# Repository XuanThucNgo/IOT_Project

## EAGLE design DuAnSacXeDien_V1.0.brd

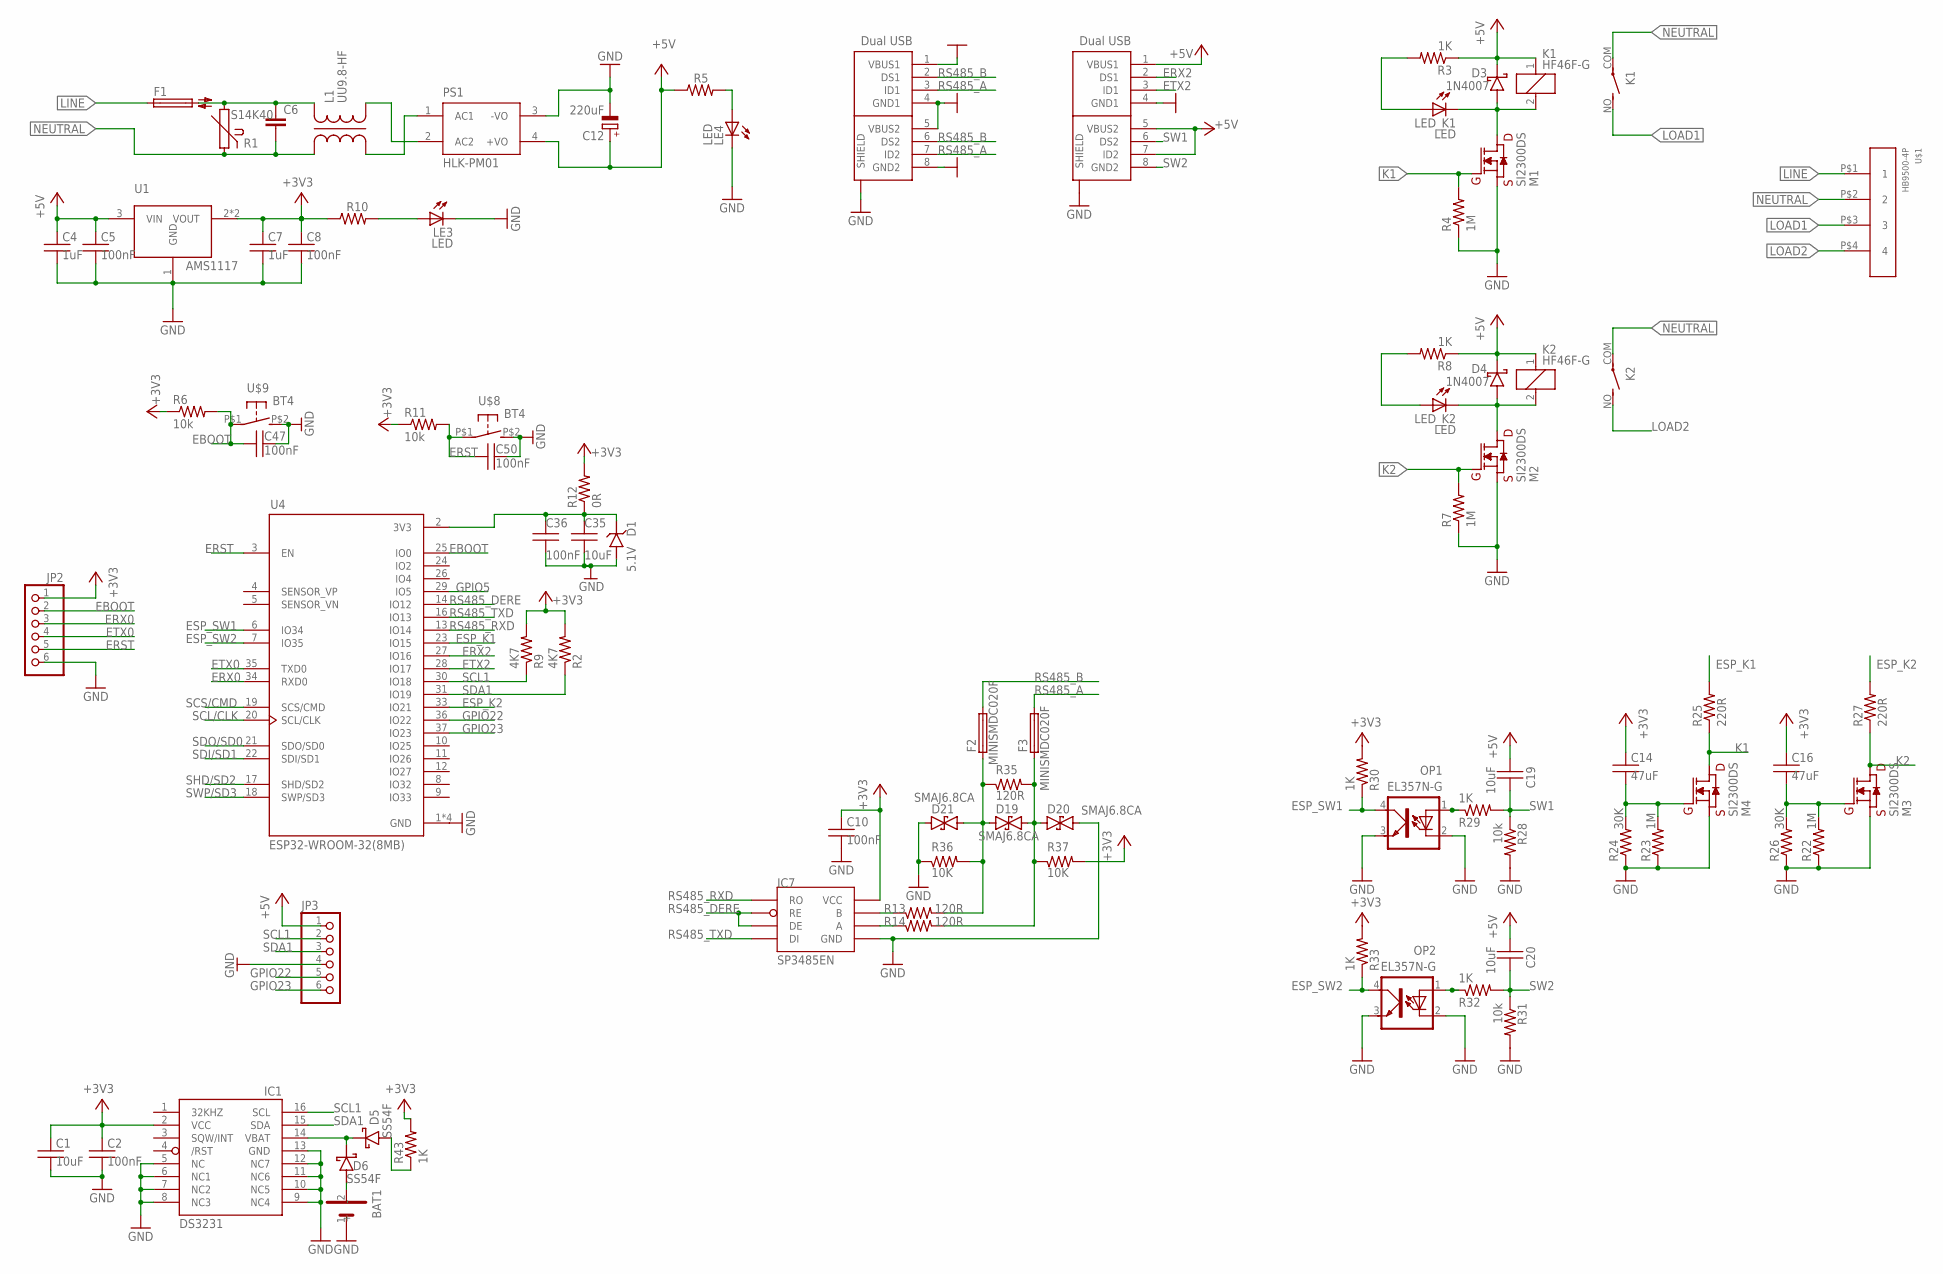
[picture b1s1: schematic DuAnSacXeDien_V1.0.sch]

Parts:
BAT1: CR1220
C1, C19, C20, C35: 10uF; 0603
C2, C5, C8, C10, C36, C47, C50: 100nF; 0603
C4, C7: 1uF; 0603
C6: C-EU150-064X183; C150-064X183
C12: 220uF; 153CLV-0605
C14, C16: 47uF; 0805
D1: 5.1V; SOD123
D3, D4: 1N4007; SMAF
D5, D6: SS54F; SMAF
D19, D20, D21: SMAJ6.8CA; DO-214AC-BI
F1: TE5
F2, F3: MINISMDC020F; C1812
IC1: DS3231/SO; SO16W
IC7: SP3485EN; SOIC-8
JP2: PINHD-1X6; 1X06
JP3: PINHD-1X6/LONG; 1X06
K1, K2: HF46F-G; LD
L1: UU9.8-HF
LE3, LE4: LED; LED3MM
LED_K1, LED_K2: LED; LED3MM
M1, M2, M3, M4: SI2300DS; SOT23(1)
OP1, OP2: EL357N-G; SOP4
PS1: HLK-PM01; HLK-PMXX
R1: S14K40
R2, R9: 4K7; 0603
R3, R5, R8, R10, R29, R30, R32, R33, R43: 1K; 0603
R4, R7, R22, R23: 1M; 0603
R6, R11, R28, R31: 10k; 0603
R12: 0R; 0603
R13, R14, R35: 120R; 0603
R24, R26: 30K; 0603
R25, R27: 220R; 0603
R36, R37: 10K; 0603
U1: LD1117; SOT223-3.3
U4: ESP32-WROOM-32(8MB); MODULE_ESP32-WROOM-32(8MB)
U$1: HB9500-4P
U$2, U$7: DUAL_USB
U$8, U$9: BT4

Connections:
+3V3: C1.1, C2.1, C7.1, C8.1, C10.1, C14.1, C16.1, IC1.2 (VCC), IC7.8 (VCC), JP2.1, R2.2, R6.1, R9.2, R10.1, R11.1, R12.2, R30.2, R33.2, R37.2, R43.2, U1.2 (VOUT), U1.4 (VOUT)
+5V: C4.1, C5.1, C12.+, C19.1, C20.1, D3.C, D4.C, JP3.1, K1.1, K2.1, PS1.4 (+VO), R3.1, R5.1, R8.1, U1.3 (VIN), U$2.1 (VBUS1), U$2.5 (VBUS2), U$2.7 (ID2)
EBOOT: C47.1, JP2.2, R6.2, U4.25 (IO0), U$9.P$1 (1)
ERST: C50.1, JP2.5, R11.2, U4.3 (EN), U$8.P$1 (1)
ERX0: JP2.3, U4.34 (RXD0)
ERX2: U4.27 (IO16), U$2.2 (DS1)
ESP_K1: R25.2, U4.23 (IO15)
ESP_K2: R27.2, U4.33 (IO21)
ESP_SW1: OP1.4 (COL), R30.1, U4.6 (IO34)
ESP_SW2: OP2.4 (COL), R33.1, U4.7 (IO35)
ETX0: JP2.4, U4.35 (TXD0)
ETX2: U4.28 (IO17), U$2.3 (ID1)
GND: BAT1.1 (-), C1.2, C2.2, C4.2, C5.2, C7.2, C8.2, C10.2, C12.-, C35.2, C36.2, C47.2, C50.2, D1.A, D20.2, D21.1, IC1.5 (NC), IC1.6 (NC1), IC1.7 (NC2), IC1.8 (NC3), IC1.9 (NC4), IC1.10 (NC5), IC1.11 (NC6), IC1.12 (NC7), IC1.13 (GND), IC7.5 (GND), JP2.6, JP3.4, LE3.K (C), LE4.K (C), M1.2 (S), M2.2 (S), M3.2 (S), M4.2 (S), OP1.2 (C), OP1.3 (EMIT), OP2.2 (C), OP2.3 (EMIT), PS1.3 (-VO), R4.1, R7.1, R22.1, R23.1, R24.1, R26.1, R28.2, R31.2, R36.1, U1.1 (GND), U4.1 (GND), U4.15 (GND), U4.38 (GND), U4.39 (GND), U$2.4 (GND1), U$2.TAB1 (SHIELD), U$2.TAB2 (SHIELD), U$2.TAB3 (SHIELD), U$2.TAB4 (SHIELD), U$7.1 (VBUS1), U$7.4 (GND1), U$7.5 (VBUS2), U$7.8 (GND2), U$7.TAB1 (SHIELD), U$7.TAB2 (SHIELD), U$7.TAB3 (SHIELD), U$7.TAB4 (SHIELD), U$8.P$2 (2), U$9.P$2 (2)
GPIO5: U4.29 (IO5)
GPIO22: JP3.5, U4.36 (IO22)
GPIO23: JP3.6, U4.37 (IO23)
K1: M1.1 (G), M4.3 (D), R4.2, R25.1
K2: M2.1 (G), M3.3 (D), R7.2, R27.1
LINE: F1.1, U$1.P$1 (1)
LOAD1: K1.NO (S), U$1.P$3 (3)
LOAD2: K2.NO (S), U$1.P$4 (4)
unnamed: D3.A, K1.2, LED_K1.K (C), M1.3 (D)
unnamed: D19.1, D21.2, F2.1, R13.2, R35.1, R36.2
unnamed: D4.A, K2.2, LED_K2.K (C), M2.3 (D)
unnamed: LED_K2.A, R8.2
unnamed: OP1.1 (A), R29.1
unnamed: LED_K1.A, R3.2
unnamed: D19.2, D20.1, F3.1, R14.2, R35.2, R37.1
unnamed: OP2.1 (A), R32.1
unnamed: C16.2, M3.1 (G), R22.2, R26.2
unnamed: C6.1, F1.2, L1.4, R1.2
unnamed: IC7.6 (A), R14.1
unnamed: IC7.7 (B), R13.1
unnamed: LE4.A, R5.2
unnamed: C35.1, C36.1, D1.C, R12.1, U4.2 (3V3)
unnamed: BAT1.2 (+), D6.A
unnamed: L1.3, PS1.2 (AC2)
unnamed: L1.2, PS1.1 (AC1)
unnamed: D5.A, R43.1
unnamed: C14.2, M4.1 (G), R23.2, R24.2
unnamed: LE3.A, R10.2
NEUTRAL: C6.2, K1.COM, K2.COM, L1.1, R1.1, U$1.P$2 (2)
RS485_A: F3.2, U$7.3 (ID1), U$7.7 (ID2)
RS485_B: F2.2, U$7.2 (DS1), U$7.6 (DS2)
RS485_DERE: IC7.2 (RE), IC7.3 (DE), U4.14 (IO12)
RS485_RXD: IC7.1 (RO), U4.13 (IO14)
RS485_TXD: IC7.4 (DI), U4.16 (IO13)
SCL1: IC1.16 (SCL), JP3.2, R9.1, U4.30 (IO18)
SCL/CLK: U4.20 (SCL/CLK)
SCS/CMD: U4.19 (SCS/CMD)
SDA1: IC1.15 (SDA), JP3.3, R2.1, U4.31 (IO19)
SDI/SD1: U4.22 (SDI/SD1)
SDO/SD0: U4.21 (SDO/SD0)
SHD/SD2: U4.17 (SHD/SD2)
SW1: C19.2, R28.1, R29.2, U$2.6 (DS2)
SW2: C20.2, R31.1, R32.2, U$2.8 (GND2)
SWP/SD3: U4.18 (SWP/SD3)
VBAT: D5.C, D6.C, IC1.14 (VBAT)

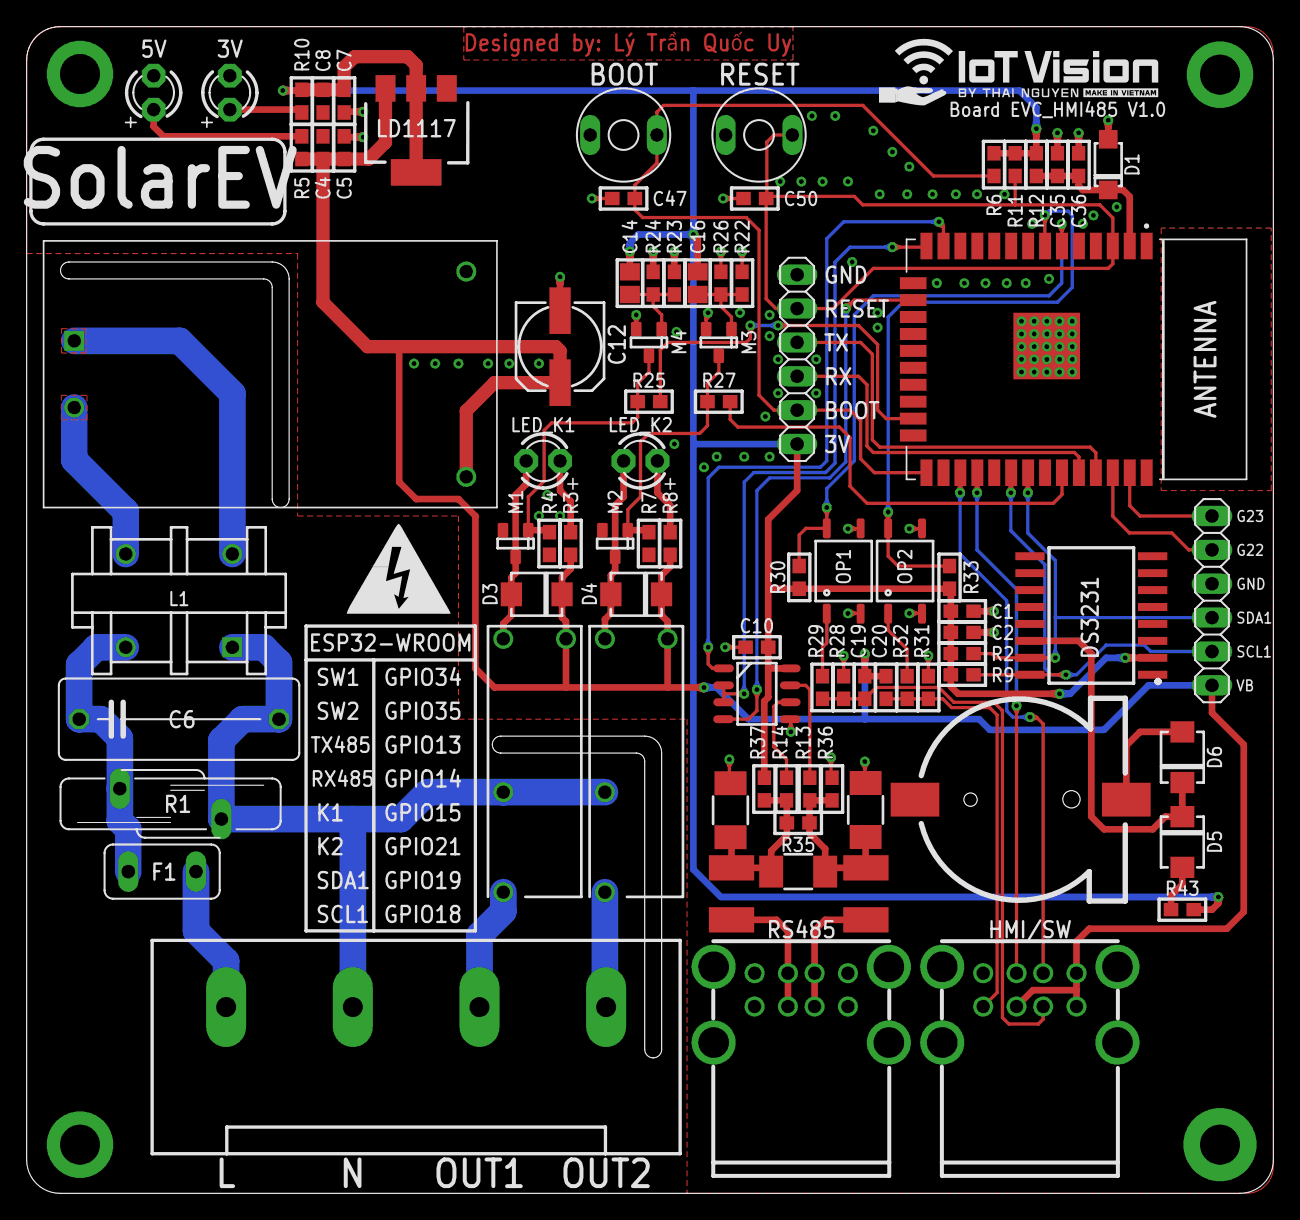
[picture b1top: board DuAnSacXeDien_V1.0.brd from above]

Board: 2 copper layers, 93.5 x 87.5 mm, 84 parts (0 on the bottom side), 51 nets.

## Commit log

2024-04-19 Thuc
